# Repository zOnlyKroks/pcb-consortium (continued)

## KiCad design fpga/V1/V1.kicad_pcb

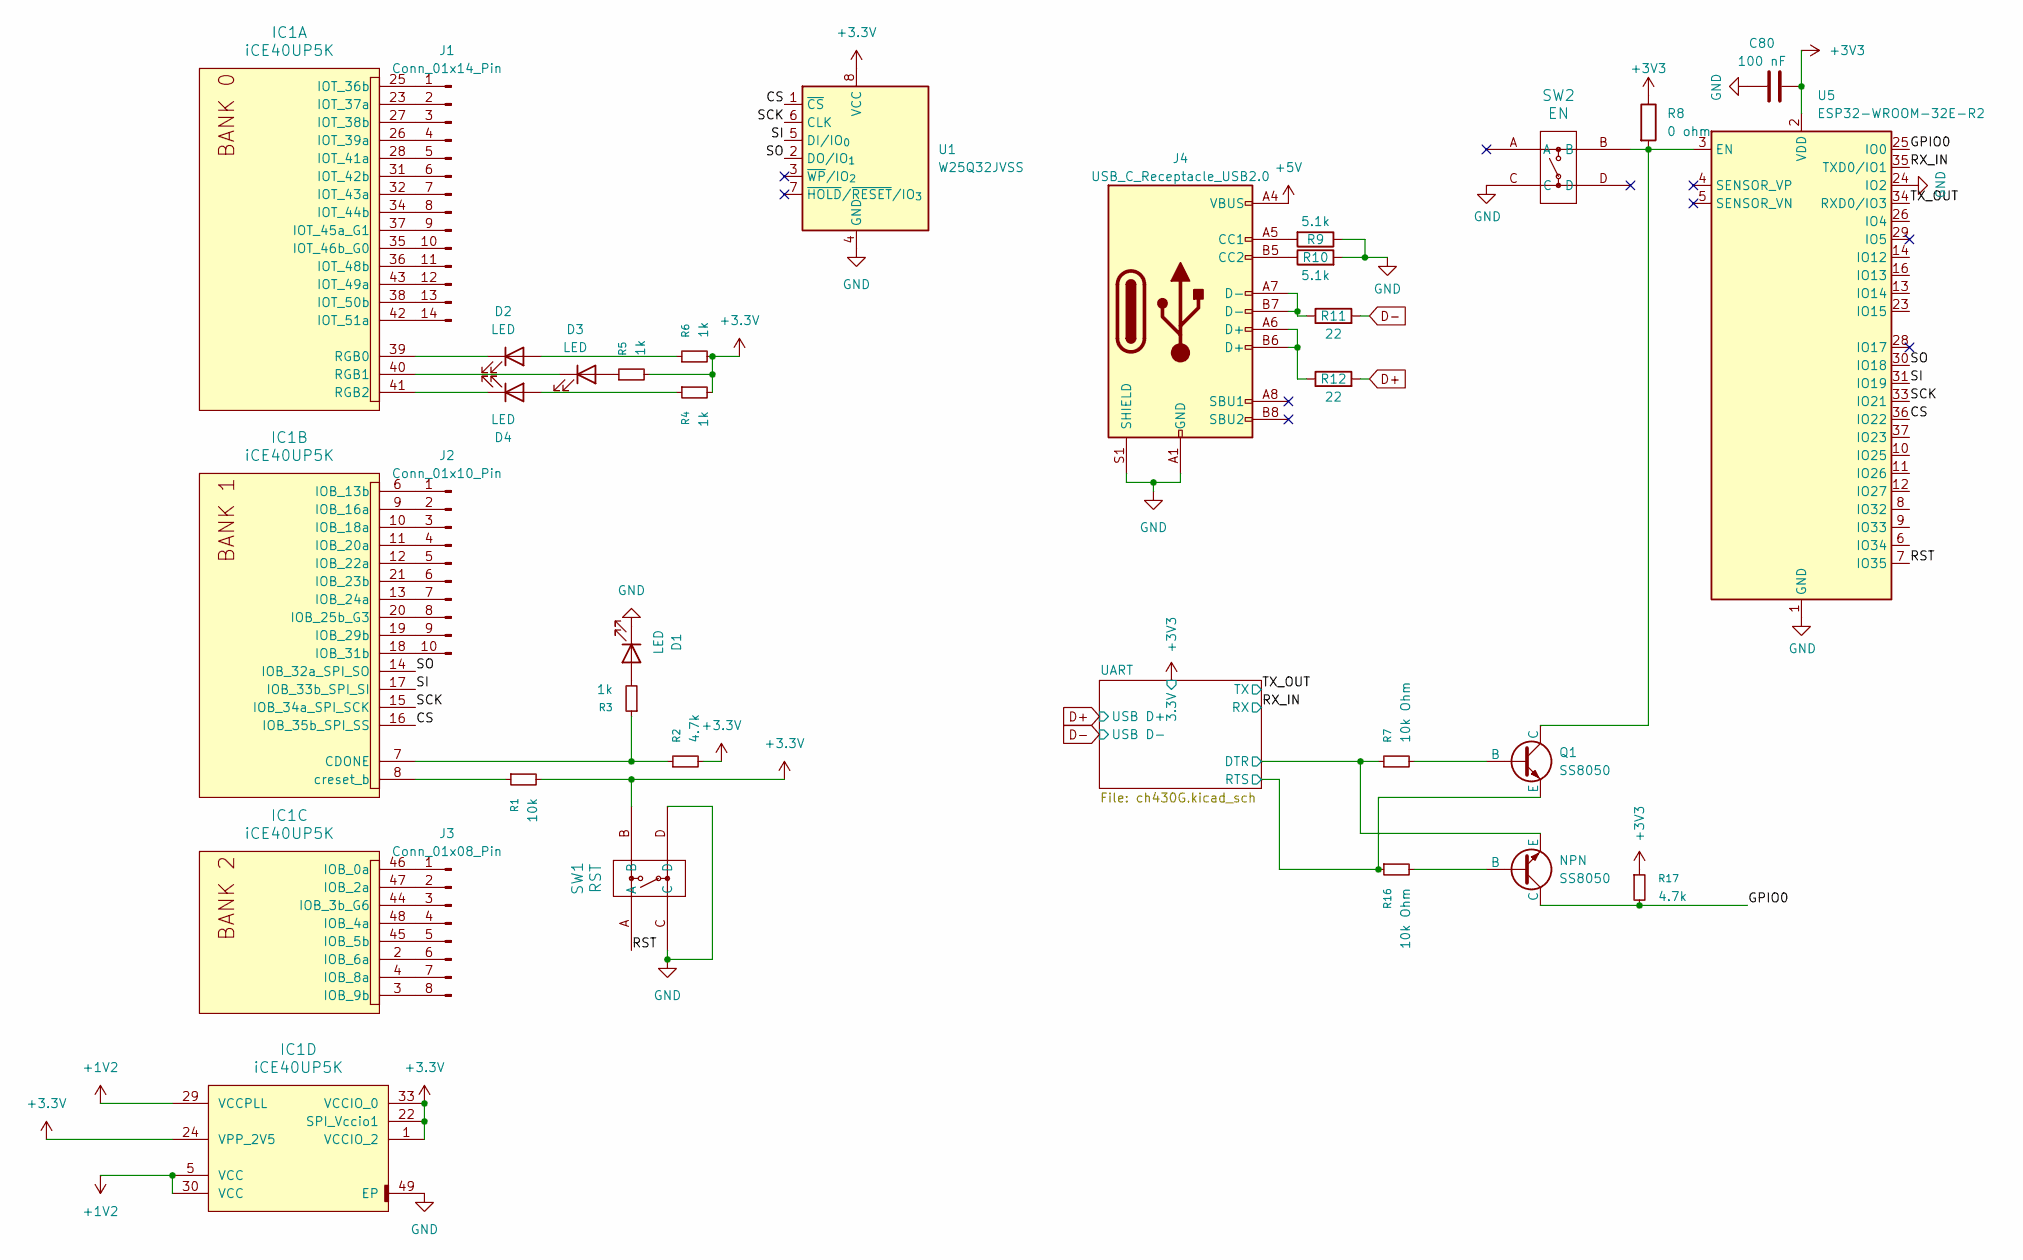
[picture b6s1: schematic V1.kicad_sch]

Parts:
C80: 100 nF; C_0805_2012Metric; LCSC Part # C49678
D1, D2, D3, D4: LED; LED_0805_2012Metric
IC1: iCE40UP5K; QFN-48-1EP_7x7mm_P0.5mm_EP5.15x5.15mm_ThermalVias
J1: Conn_01x14_Pin; PinHeader_1x14_P2.54mm_Vertical
J2: Conn_01x10_Pin; PinHeader_1x10_P2.54mm_Vertical
J3: Conn_01x08_Pin; PinHeader_1x08_P2.54mm_Vertical
J4: USB_C_Receptacle_USB2.0; USB_C_Receptacle_HRO_TYPE-C-31-M-12; JlcRotOffset 180
Q1: SS8050; SOT-23
R1: 10k; R_0603_1608Metric
R2: 4.7k; R_0603_1608Metric
R3, R4, R5, R6: 1k; R_0603_1608Metric
R7, R16: 10k Ohm; R_0805_2012Metric
R8: 0 ohm; R_0805_2012Metric; LCSC Part # C17477
R9, R10: 5.1k; R_0805_2012Metric; LCSC Part # C27834
R11, R12: 22; R_0805_2012Metric; LCSC Part # C17561
R17: 4.7k; R_0603_1608Metric; LCSC Part # C23162
SS8050: NPN; SOT-23
SW1: RST; KH-6X6X5H-STM_SKE
SW2: EN; KH-6X6X5H-STM_SKE; LCSC Part # C2837531
U1: W25Q32JVSS; SOIC-8_5.3x5.3mm_P1.27mm
U5: ESP32-WROOM-32E-R2; ESP32-WROOM-32D

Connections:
+1V2: IC1.5 (VCC), IC1.29 (VCCPLL), IC1.30 (VCC)
+3.3V: IC1.1 (VCCIO_2), IC1.22 (SPI_Vccio1), IC1.24 (VPP_2V5), IC1.33 (VCCIO_0), R1.2, R2.2, R4.2, R5.2, R6.2, SW1.B, U1.8 (VCC)
+3V3: C80.1, R8.1, R17.1, U5.2 (VDD); also elsewhere on the board
+5V: J4.A4 (VBUS), J4.A9 (VBUS), J4.B4 (VBUS), J4.B9 (VBUS)
/CS: IC1.16 (IOB_35b_SPI_SS), U1.1 (~CS), U5.36 (IO22)
/GPIO0: R17.2, SS8050.1 (C), U5.25 (IO0)
/RST: SW1.A, U5.7 (IO35)
/RX_IN: U5.35 (TXD0/IO1); also elsewhere on the board
/SCK: IC1.15 (IOB_34a_SPI_SCK), U1.6 (CLK), U5.33 (IO21)
/SI: IC1.17 (IOB_33b_SPI_SI), U1.5 (DI/IO_{0}), U5.31 (IO19)
/SO: IC1.14 (IOB_32a_SPI_SO), U1.2 (DO/IO_{1}), U5.30 (IO18)
/TX_OUT: U5.34 (RXD0/IO3); also elsewhere on the board
/UART/DTR: R7.1, SS8050.3 (E); also elsewhere on the board
/UART/RTS: Q1.3 (E), R16.1; also elsewhere on the board
D+: R12.2; also elsewhere on the board
D-: R11.2; also elsewhere on the board
GND: C80.2, D1.1 (K), IC1.49 (EP), J4.A1 (GND), J4.A12 (GND), J4.B1 (GND), J4.B12 (GND), J4.S1 (SHIELD), R9.1, R10.2, SW1.C, SW1.D, SW2.C, U1.4 (GND), U5.1 (GND), U5.15 (GND), U5.24 (IO2), U5.38 (GND), U5.39 (GND); also elsewhere on the board
unnamed: D1.2 (A), R3.2
unnamed: D2.2 (A), R6.1
unnamed: D2.1 (K), IC1.39 (RGB0)
unnamed: D3.2 (A), R5.1
unnamed: D3.1 (K), IC1.40 (RGB1)
unnamed: D4.2 (A), R4.1
unnamed: D4.1 (K), IC1.41 (RGB2)
unnamed: IC1.25 (IOT_36b), J1.1
unnamed: IC1.23 (IOT_37a), J1.2
unnamed: IC1.27 (IOT_38b), J1.3
unnamed: IC1.26 (IOT_39a), J1.4
unnamed: IC1.28 (IOT_41a), J1.5
unnamed: IC1.31 (IOT_42b), J1.6
unnamed: IC1.32 (IOT_43a), J1.7
unnamed: IC1.34 (IOT_44b), J1.8
unnamed: IC1.37 (IOT_45a_G1), J1.9
unnamed: IC1.35 (IOT_46b_G0), J1.10
unnamed: IC1.36 (IOT_48b), J1.11
unnamed: IC1.43 (IOT_49a), J1.12
unnamed: IC1.38 (IOT_50b), J1.13
unnamed: IC1.42 (IOT_51a), J1.14
unnamed: IC1.7 (CDONE), R2.1, R3.1
unnamed: IC1.6 (IOB_13b), J2.1
unnamed: IC1.9 (IOB_16a), J2.2
unnamed: IC1.10 (IOB_18a), J2.3
unnamed: IC1.11 (IOB_20a), J2.4
unnamed: IC1.12 (IOB_22a), J2.5
unnamed: IC1.21 (IOB_23b), J2.6
unnamed: IC1.13 (IOB_24a), J2.7
unnamed: IC1.20 (IOB_25b_G3), J2.8
unnamed: IC1.19 (IOB_29b), J2.9
unnamed: IC1.18 (IOB_31b), J2.10
unnamed: IC1.8 (creset_b), R1.1
unnamed: IC1.46 (IOB_0a), J3.1
unnamed: IC1.47 (IOB_2a), J3.2
unnamed: IC1.44 (IOB_3b_G6), J3.3
unnamed: IC1.48 (IOB_4a), J3.4
unnamed: IC1.45 (IOB_5b), J3.5
unnamed: IC1.2 (IOB_6a), J3.6
unnamed: IC1.4 (IOB_8a), J3.7
unnamed: IC1.3 (IOB_9b), J3.8
unnamed: J4.A5 (CC1), R9.2
unnamed: J4.B5 (CC2), R10.1
unnamed: J4.A6 (D+), J4.B6 (D+), R12.1
unnamed: J4.A7 (D-), J4.B7 (D-), R11.1
unnamed: Q1.2 (B), R7.2
unnamed: Q1.1 (C), R8.2, SW2.B, U5.3 (EN)
unnamed: R16.2, SS8050.2 (B)

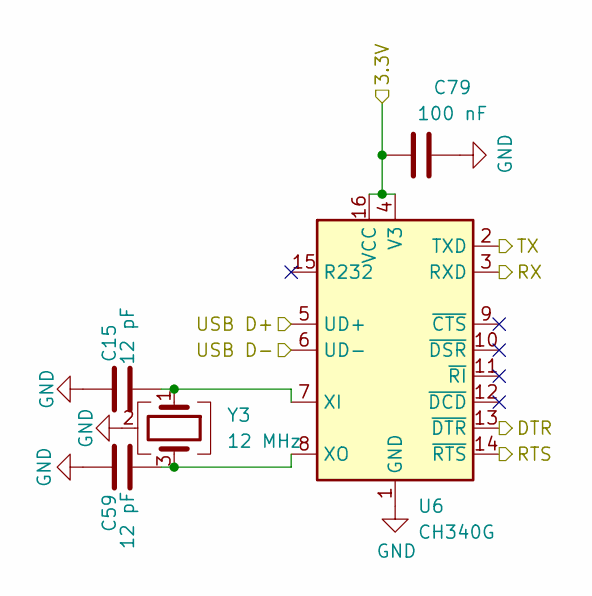
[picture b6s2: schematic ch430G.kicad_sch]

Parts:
C15, C59: 12 pF; C_0805_2012Metric; LCSC Part # C107108
C79: 100 nF; C_0805_2012Metric; LCSC Part # C49678
U6: CH340G; SOIC-16_3.9x9.9mm_P1.27mm
Y3: 12 MHz; Crystal_SMD_3225-4Pin_3.2x2.5mm; LCSC Part # C19631429

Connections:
+3V3: C79.2, U6.4 (V3), U6.16 (VCC); also elsewhere on the board
/RX_IN: U6.3 (RXD); also elsewhere on the board
/TX_OUT: U6.2 (TXD); also elsewhere on the board
/UART/DTR: U6.13 (~DTR); also elsewhere on the board
/UART/RTS: U6.14 (~RTS); also elsewhere on the board
D+: U6.5 (UD+); also elsewhere on the board
D-: U6.6 (UD-); also elsewhere on the board
GND: C15.1, C59.1, C79.1, U6.1 (GND), Y3.2 (G), Y3.4 (G); also elsewhere on the board
unnamed: C15.2, U6.7 (XI), Y3.1
unnamed: C59.2, U6.8 (XO), Y3.3

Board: 2 copper layers, 35 parts (0 on the bottom side), 67 nets, no tracks yet.
